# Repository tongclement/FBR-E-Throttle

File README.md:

## Resources

- [PID Controller in C](https://deepbluembedded.com/esp32-timers-timer-interrupt-tutorial-arduino-ide/)
- [ESP32 Arduino IDE Timer Interrupts Reference](https://deepbluembedded.com/esp32-timers-timer-interrupt-tutorial-arduino-ide/)

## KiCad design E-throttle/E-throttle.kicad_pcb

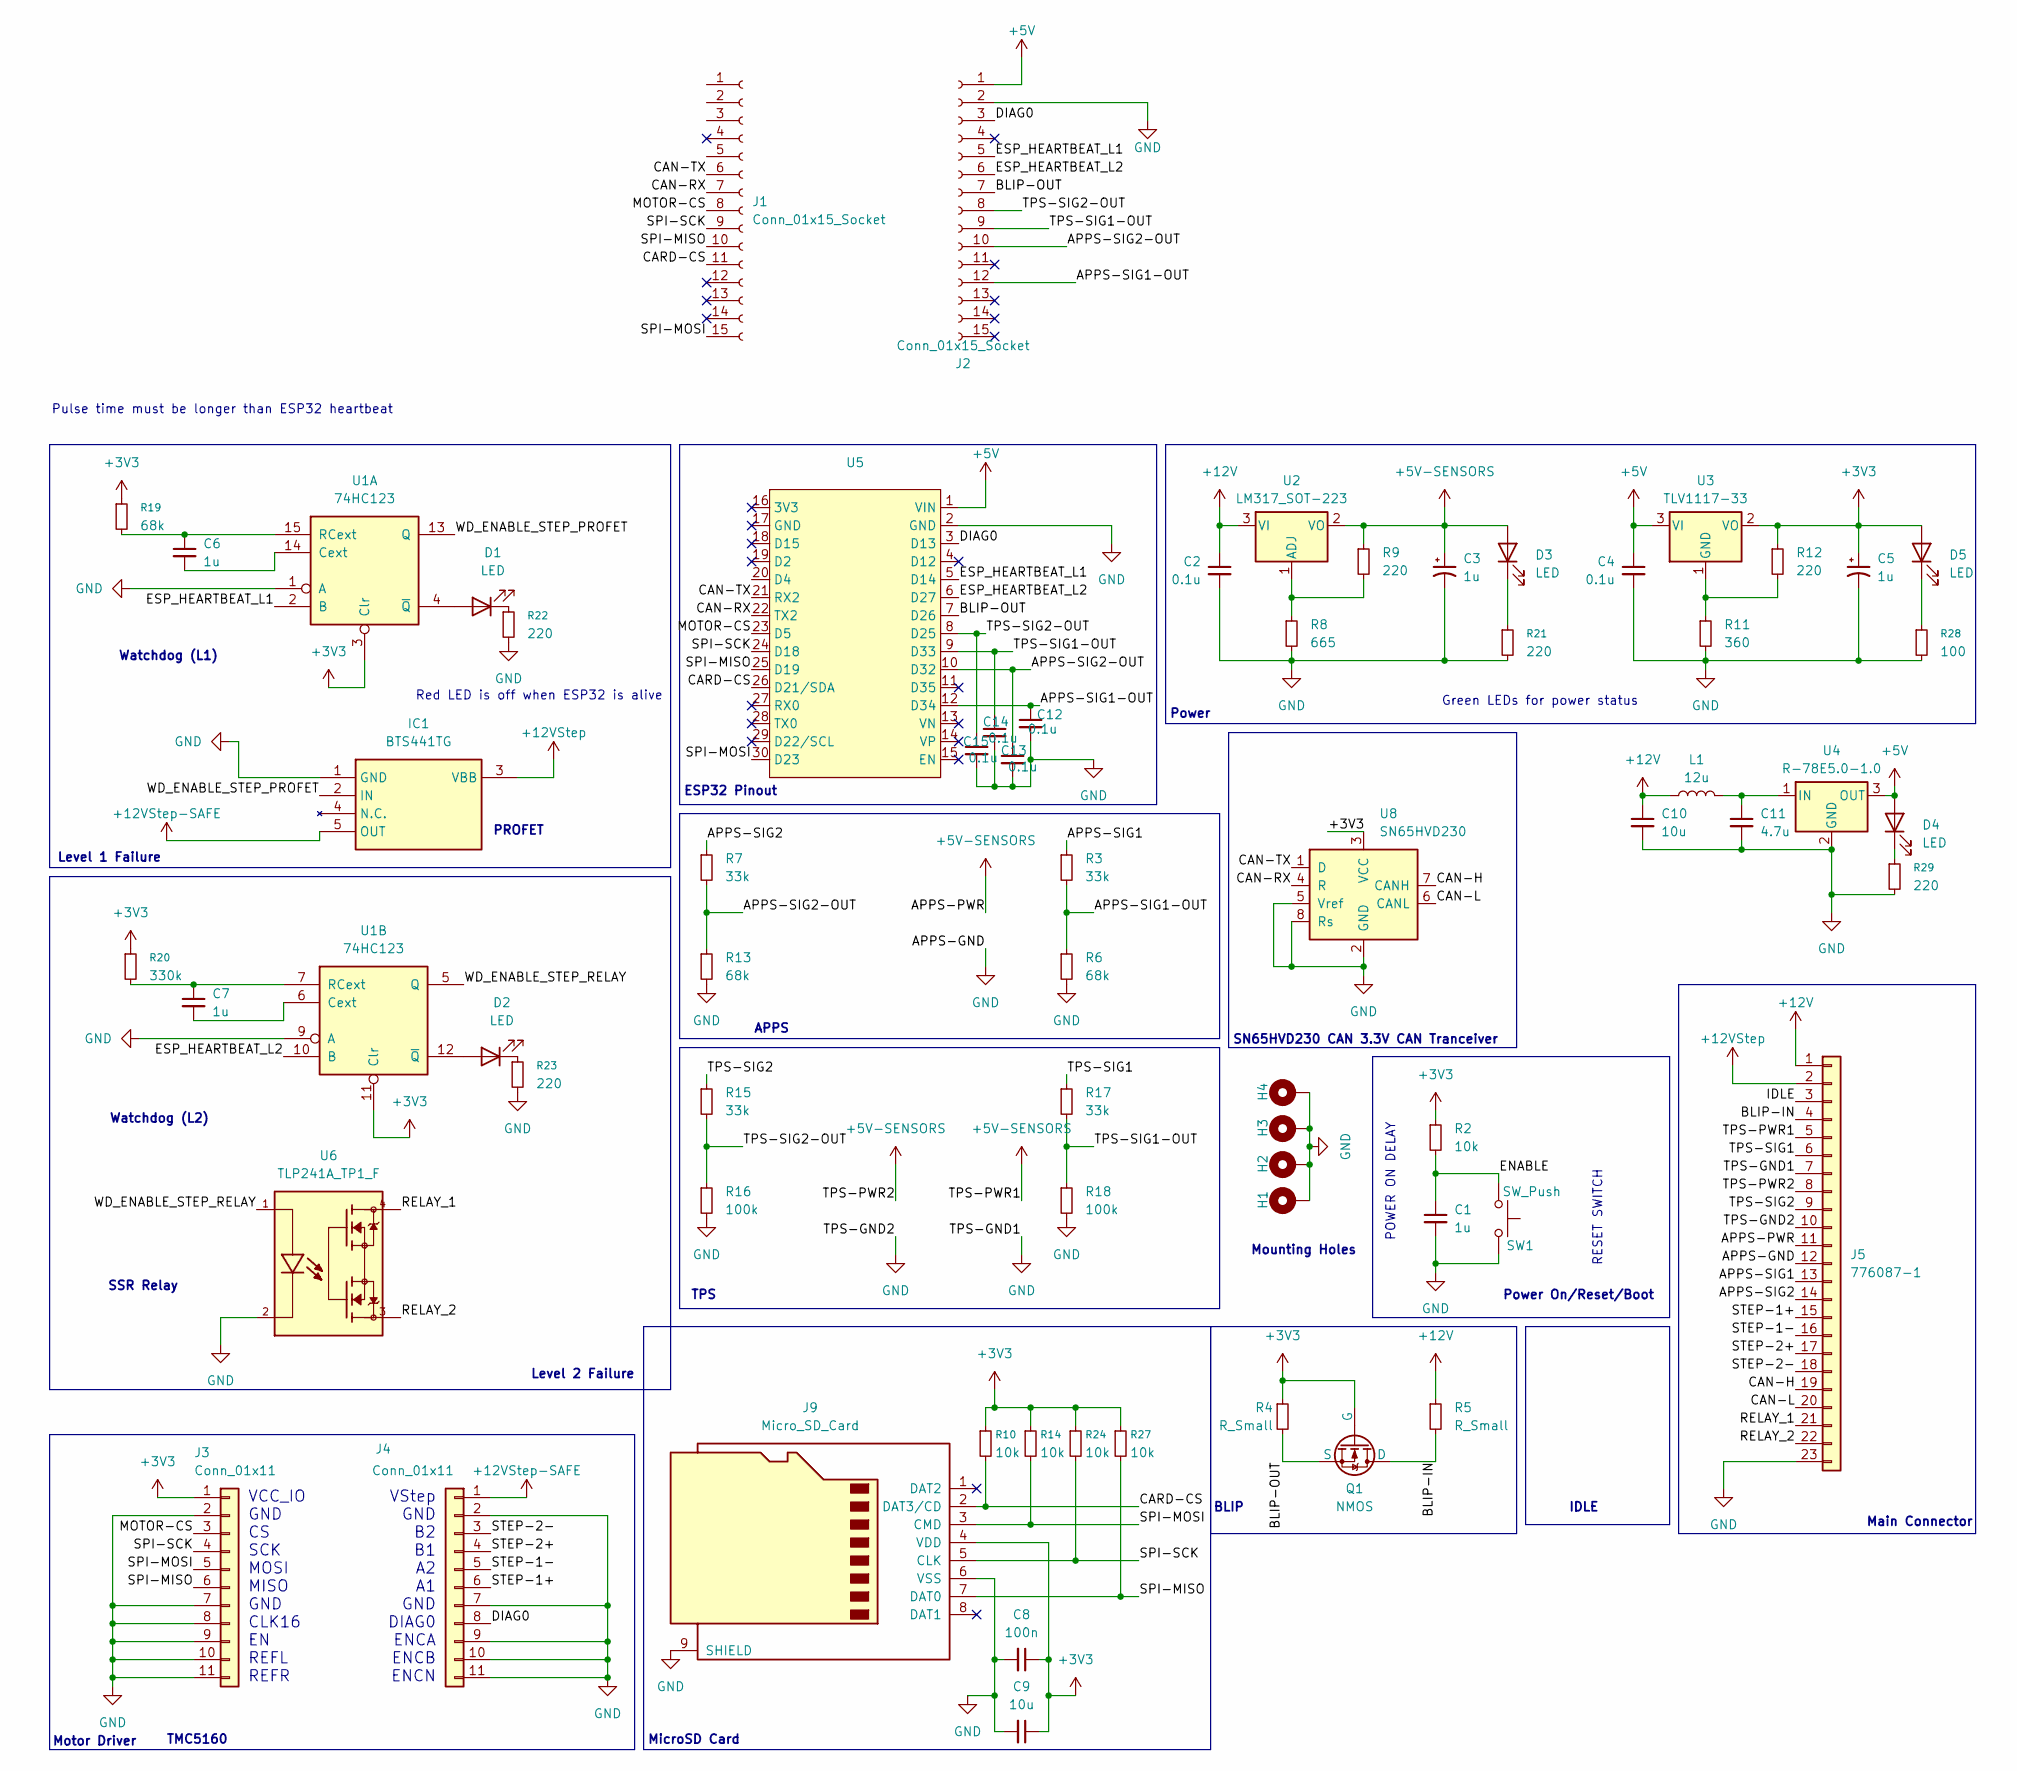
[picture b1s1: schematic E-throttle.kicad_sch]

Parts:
C1, C3, C5, C6, C7: 1u; C_0805_2012Metric
C2, C4: 0.1u; C_0805_2012Metric
C8: 100n; C_0805_2012Metric
C9: 10u; C_0805_2012Metric
C10: 10u; C_0603_1608Metric_Pad1.08x0.95mm_HandSolder
C11: 4.7u; C_0603_1608Metric_Pad1.08x0.95mm_HandSolder
C12, C13, C14, C15: 0.1u; C_Radial_D4.0mm_H7.0mm_P1.50mm
D1, D2: LED; LED_D5.0mm
D3, D4, D5: LED; LED_0805_2012Metric_Pad1.15x1.40mm_HandSolder
H1, H2, H3, H4: MountingHole_Pad; MountingHole_3.2mm_M3_Pad_Via
IC1: BTS441TG; Mouser Part Number 726-BTS441TG
J1, J2: Conn_01x15_Socket; PinSocket_1x15_P2.54mm_Vertical
J3, J4: Conn_01x11; PinSocket_1x11_P2.54mm_Vertical
J5: 776087-1; TE_776087-1
J9: Micro_SD_Card; microSD_HC_Wuerth_693072010801
L1: 12u; L_6.3x6.3_H3
Q1: NMOS; TO-263-3_TabPin2
R2, R10, R14, R24, R27: 10k; R_0805_2012Metric
R3, R7, R15, R17: 33k; R_0805_2012Metric
R4, R5: R_Small; R_0805_2012Metric
R6, R13, R19: 68k; R_0805_2012Metric
R8: 665; R_0805_2012Metric
R9, R12, R21, R22, R23, R29: 220; R_0805_2012Metric
R11: 360; R_0805_2012Metric
R16, R18: 100k; R_0805_2012Metric
R20: 330k; R_0805_2012Metric
R28: 100; R_0805_2012Metric
SW1: SW_Push; SW_PUSH_1P1T_6x3.5mm_H4.3_APEM_MJTP1243
U1: 74HC123; SOIC-16_3.9x9.9mm_P1.27mm
U2: LM317_SOT-223; SOT-223-3_TabPin2
U3: TLV1117-33; TO-252-3_TabPin2
U4: R-78E5.0-1.0; Converter_DCDC_RECOM_R-78E-0.5_THT
U5: ESP32_30pin
U6: TLP241A_TP1_F; SOIC254P1000X425-4N; PARTREV 7.0
U8: SN65HVD230; SOIC-8_3.9x4.9mm_P1.27mm

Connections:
+3V3: C5.1, C8.1, C9.1, D5.2 (A), J3.1, J9.4 (VDD), Q1.2 (G), R2.1, R4.1, R10.1, R12.1, R14.1, R19.1, R20.1, R24.1, R27.1, U1.3 (Clr), U1.11 (Clr), U3.2 (VO), U8.3 (VCC)
+5V: C4.1, D4.2 (A), J2.1, U3.3 (VI), U4.3 (OUT), U5.1 (VIN)
+5V-SENSORS: C3.1, D3.2 (A), J5.5, J5.8, J5.11, R9.1, U2.2 (VO)
+12V: C2.1, C10.1, J5.1, L1.1, R5.1, U2.3 (VI)
+12VStep: IC1.3 (VBB), J5.2
+12VStep-SAFE: IC1.5 (OUT), J4.1
/APPS-SIG1: J5.13, R3.1
/APPS-SIG1-OUT: C12.1, J2.12, R3.2, R6.1, U5.12 (D34)
/APPS-SIG2: J5.14, R7.1
/APPS-SIG2-OUT: C13.1, J2.10, R7.2, R13.1, U5.10 (D32)
/BLIP-IN: J5.4, Q1.1 (D), R5.2
/BLIP-OUT: J2.7, Q1.3 (S), R4.2, U5.7 (D26)
/CAN-H: J5.19, U8.7 (CANH)
/CAN-L: J5.20, U8.6 (CANL)
/CAN-RX: J1.7, U5.22 (TX2), U8.4 (R)
/CAN-TX: J1.6, U5.21 (RX2), U8.1 (D)
/CARD-CS: J1.11, J9.2 (DAT3/CD), R10.2, U5.26 (D21/SDA)
/DIAG0: J2.3, J4.8, U5.3 (D13)
/ENABLE: C1.1, R2.2, SW1.1
/ESP_HEARTBEAT_L1: J2.5, U1.2 (B), U5.5 (D14)
/ESP_HEARTBEAT_L2: J2.6, U1.10 (B), U5.6 (D27)
/IDLE: J5.3
/MOTOR-CS: J1.8, J3.3, U5.23 (D5)
/RELAY_1: J5.21, U6.4
/RELAY_2: J5.22, U6.3
/SPI-MISO: J1.10, J3.6, J9.7 (DAT0), R27.2, U5.25 (D19)
/SPI-MOSI: J1.15, J3.5, J9.3 (CMD), R14.2, U5.30 (D23)
/SPI-SCK: J1.9, J3.4, J9.5 (CLK), R24.2, U5.24 (D18)
/STEP-1+: J4.6, J5.15
/STEP-1-: J4.5, J5.16
/STEP-2+: J4.4, J5.17
/STEP-2-: J4.3, J5.18
/TPS-SIG1: J5.6, R17.1
/TPS-SIG1-OUT: C14.1, J2.9, R17.2, R18.1, U5.9 (D33)
/TPS-SIG2: J5.9, R15.1
/TPS-SIG2-OUT: C15.1, J2.8, R15.2, R16.1, U5.8 (D25)
/WD_ENABLE_STEP_PROFET: IC1.2 (IN), U1.13 (Q)
/WD_ENABLE_STEP_RELAY: U1.5 (Q), U6.1
GND: C1.2, C2.2, C3.2, C4.2, C5.2, C8.2, C9.2, C10.2, C11.2, C12.2, C13.2, C14.2, C15.2, H1.1, H2.1, H3.1, H4.1, IC1.1 (GND), J2.2, J3.2, J3.7, J3.8, J3.9, J3.10, J3.11, J4.2, J4.7, J4.9, J4.10, J4.11, J5.7, J5.10, J5.12, J5.23, J9.6 (VSS), J9.9 (SHIELD), R6.2, R8.2, R11.2, R13.2, R16.2, R18.2, R21.2, R22.2, R23.2, R28.2, R29.2, SW1.2, U1.1 (A), U1.9 (A), U4.2 (GND), U5.2 (GND), U6.2, U8.2 (GND), U8.5 (Vref), U8.8 (Rs)
unnamed: D1.2 (A), U1.4 (~Q)
unnamed: D1.1 (K), R22.1
unnamed: D2.2 (A), U1.12 (~Q)
unnamed: D2.1 (K), R23.1
unnamed: D3.1 (K), R21.1
unnamed: D4.1 (K), R29.1
unnamed: D5.1 (K), R28.1
unnamed: C6.2, U1.14 (Cext)
unnamed: C6.1, R19.2, U1.15 (RCext)
unnamed: C7.2, U1.6 (Cext)
unnamed: C7.1, R20.2, U1.7 (RCext)
unnamed: R8.1, R9.2, U2.1 (ADJ)
unnamed: R11.1, R12.2, U3.1 (GND)
unnamed: C11.1, L1.2, U4.1 (IN)

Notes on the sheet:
Motor Driver
PROFET
VStep GND B2 B1 A2 A1 GND DIAG0 ENCA ENCB ENCN
Level 2 Failure
Green LEDs for power status
Pulse time must be longer than ESP32 heartbeat
Red LED is off when ESP32 is alive
TPS
Mounting Holes
Power
Level 1 Failure
ESP32 Pinout
MicroSD Card
RESET SWITCH
POWER ON DELAY
BLIP
Main Connector
IDLE
Watchdog (L1)
TMC5160
VCC_IO GND CS SCK MOSI MISO GND CLK16 EN REFL REFR
SSR Relay
APPS
Power On/Reset/Boot
Watchdog (L2)
SN65HVD230 CAN 3.3V CAN Tranceiver

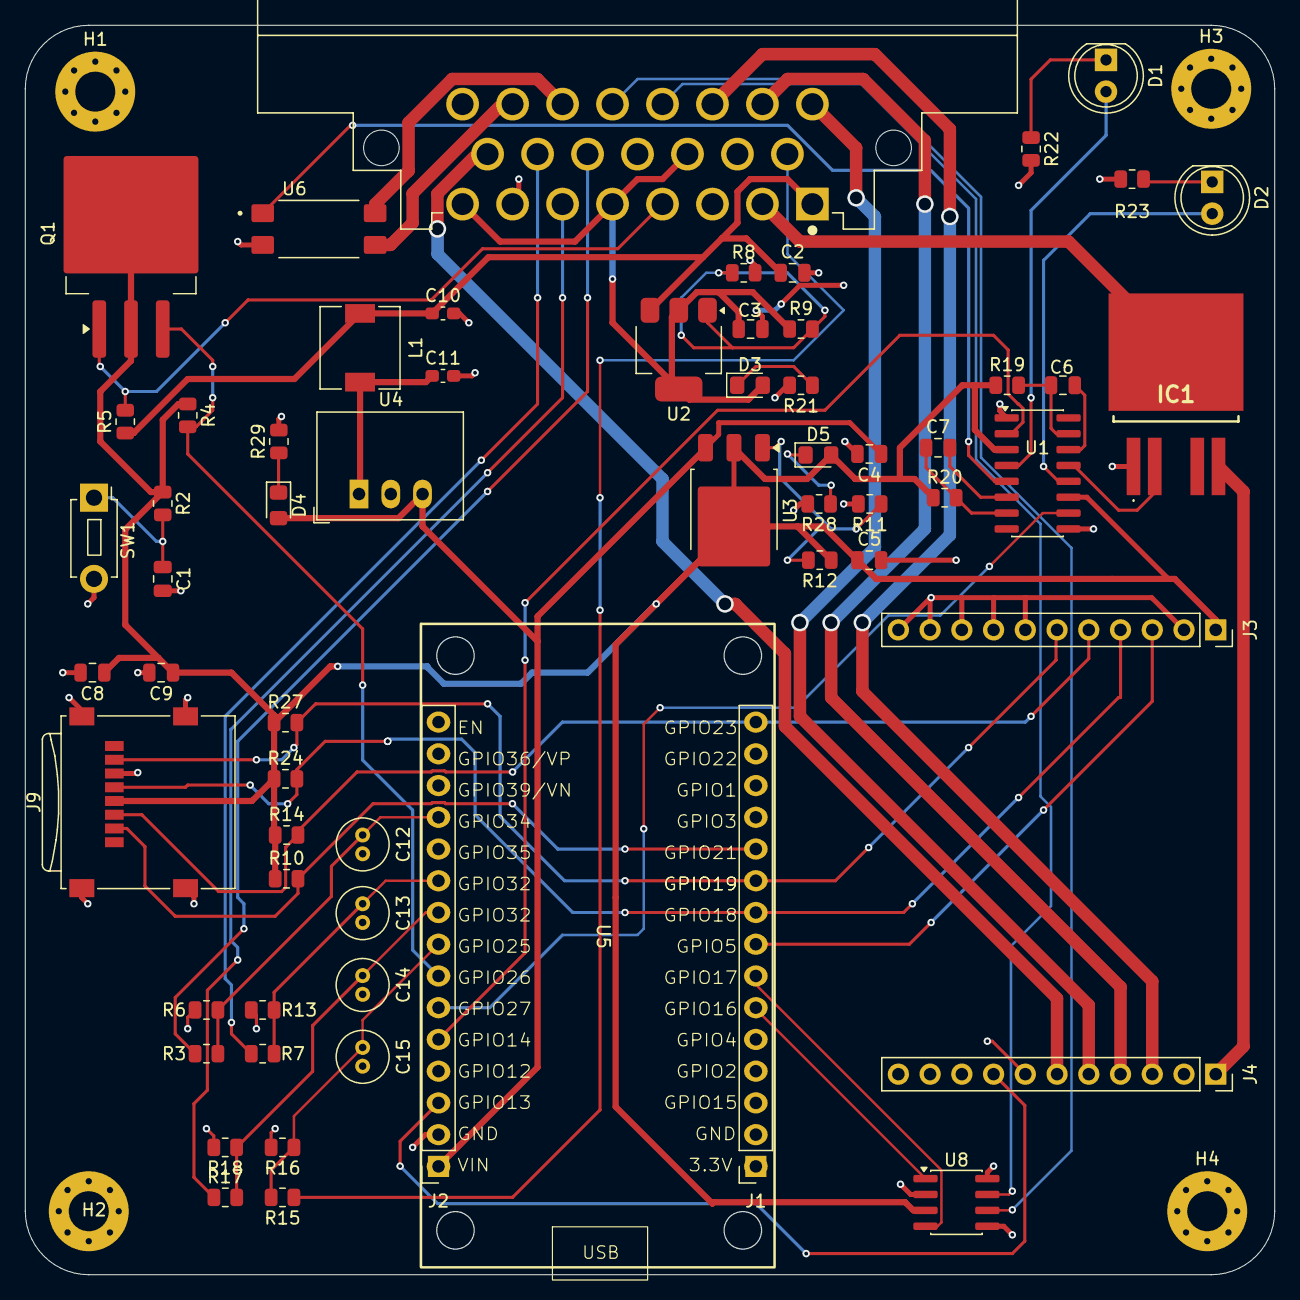
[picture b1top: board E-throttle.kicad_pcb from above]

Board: 2 copper layers, 99.9 x 99.9 mm, 68 parts (1 on the bottom side), 52 nets.

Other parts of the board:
E-Throttle (2026): LOGO; FBR_Logo_.9in

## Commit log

2025-01-25 Original Files from Nod
2025-02-08 Lock file removed, ready for wiring.
2025-02-09 Completed wiring 2.0
2025-02-19 Run DRC, generate Gerbers
2026-01-27 Added stepper motor and APPS code
    Stepper motor movement mapped from APPS sensor reading
2026-01-29 Add potential PID controller code
2026-01-29 Add README.md with resources
2026-02-01 Added simultaneous reading of TPPS and APPS
2026-02-01 Added sensor readings for both APPS sensors
2026-02-08 Implemented RTOS Task, switching from Interupt Timer
    8/2/26
2026-02-08 this version doesnt work
2026-02-27 Updated PCB for 2026 (v0.1)
    - Switch from ESP32 S3 Wroom1 Module to ESP dev board (Todo: Check Power Supply to ESP32 and other components)
    - Fixed incorrect TPS wiring (replaced variable resistors)
    - Did not reconnect JTAG debugger and programmer to ESP32 Dev Board
    - Did not reconnect CAN Transceiver
2026-02-27 Implemented Level 1 Failure Circuit
    - Added Hardware Watchdog (74HC123) that requires ESP32 to send "Heartbeat" alive signal every 20ms, or else the stepper motor power gets cut
    - ⁠Added PROFET / Automotive Smart High-Side Switch (BTS441TG) to cut power to the stepper motor, if the hardware watchdog doesn't receive a heartbeat from the ESP32 within the required timeframe (We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
2026-03-01 Updated schematic based on today's discussions
    Updated:
    - Second Watchdog with independent ESP heartbeat
    - Relay pins (21 and 22) from connector
    - BLIP and IDLE connected to ESP GPIO pins
    Not Added Yet:
    - Relay
2026-03-08 Added MicroSD Card to schematic
2026-03-08 Added status LEDs, reorganized schematic
2026-03-08 Added relay, added all footprints to schematic
2026-03-15 Initial PCB Layout edit
    - Added ESP32 Dev Board footprint
    - Expanded PCB layout edges
    - Added all components in new layout
2026-03-15 Adjusted layout, added ground plane
2026-03-16 Finalized Schematic (added power status LEDs, pull-up resistors for SD, separate 5V power) - not reviewed yet
2026-03-16 (Actually) finalized schematic - added status LED for 12V supply - need to review
2026-03-16 arranged components
2026-03-17 Added majority of routing to PCB layout
2026-03-18 added a few ground vias
2026-03-18 Fix Stepper Driver Spacing
2026-03-19 added vias, ran DRC
2026-03-19 Added THT filtering capacitors
2026-03-19 Added FBR Logo
2026-03-19 Ran DRC - fixed all errors
2026-03-19 Added Pin Sockets on top of ESP32 Dev Board footprint
    Set ESP32 Dev board to be a ghost footprint (not included in BOM, coordinates, etc)
    Added 2 1x15 female pin headers to the schematic, assigned them footprints, and aligned the precisely over the U5 pads using magnetic snapping to guarantee 25.4mm pitch
2026-03-19 Changed Stepper motor driver headers to female headers
2026-03-19 Deleted IDLE Control circuit
    Fully disconnected IDLE control pin from loom
2026-03-20 Fixed clearance issues to comply with DRC
2026-03-20 changed 3V3 votlage regulator
2026-03-20 changed some resistor values
2026-03-20 pre-PCBA misc changes
2026-04-16 some more routing
2026-04-21 temp code (doesn't work)
2026-04-22 still does't work
2026-05-24 PCB testing scripts
    Added heartbeat test
    Edited pin number inconsistencies
2026-06-25 Transitioned to PlatformIO - Stepper Motor Works
    Tested with Throttle Position Sensor Unplugged
    Stepper motor spins forwards and backwards repeatedly every few seconds with great power. It works.
2026-06-29 Rewrote Code to PlatformIO (was originally placed in the wrong directory so it wasn't committed)
    Now takes reading of APPS 1 Only (Does not use APPS 2 as without the pedal box, it's hard to move both APPS 1 and 2 simultaneously without triggering an APPS disagree error
    And moves the stepper motor proportionally
    Does not use TPS / feedback, as the Throttle wasn't installed yet at the time.
    The Stepper Motor and APPS 1 works as intended
